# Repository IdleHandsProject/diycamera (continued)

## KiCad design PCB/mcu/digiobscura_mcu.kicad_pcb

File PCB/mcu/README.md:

# Sensory_Adaptation_Bot
A Neural network robot for learning new sensors without programming them specifically.

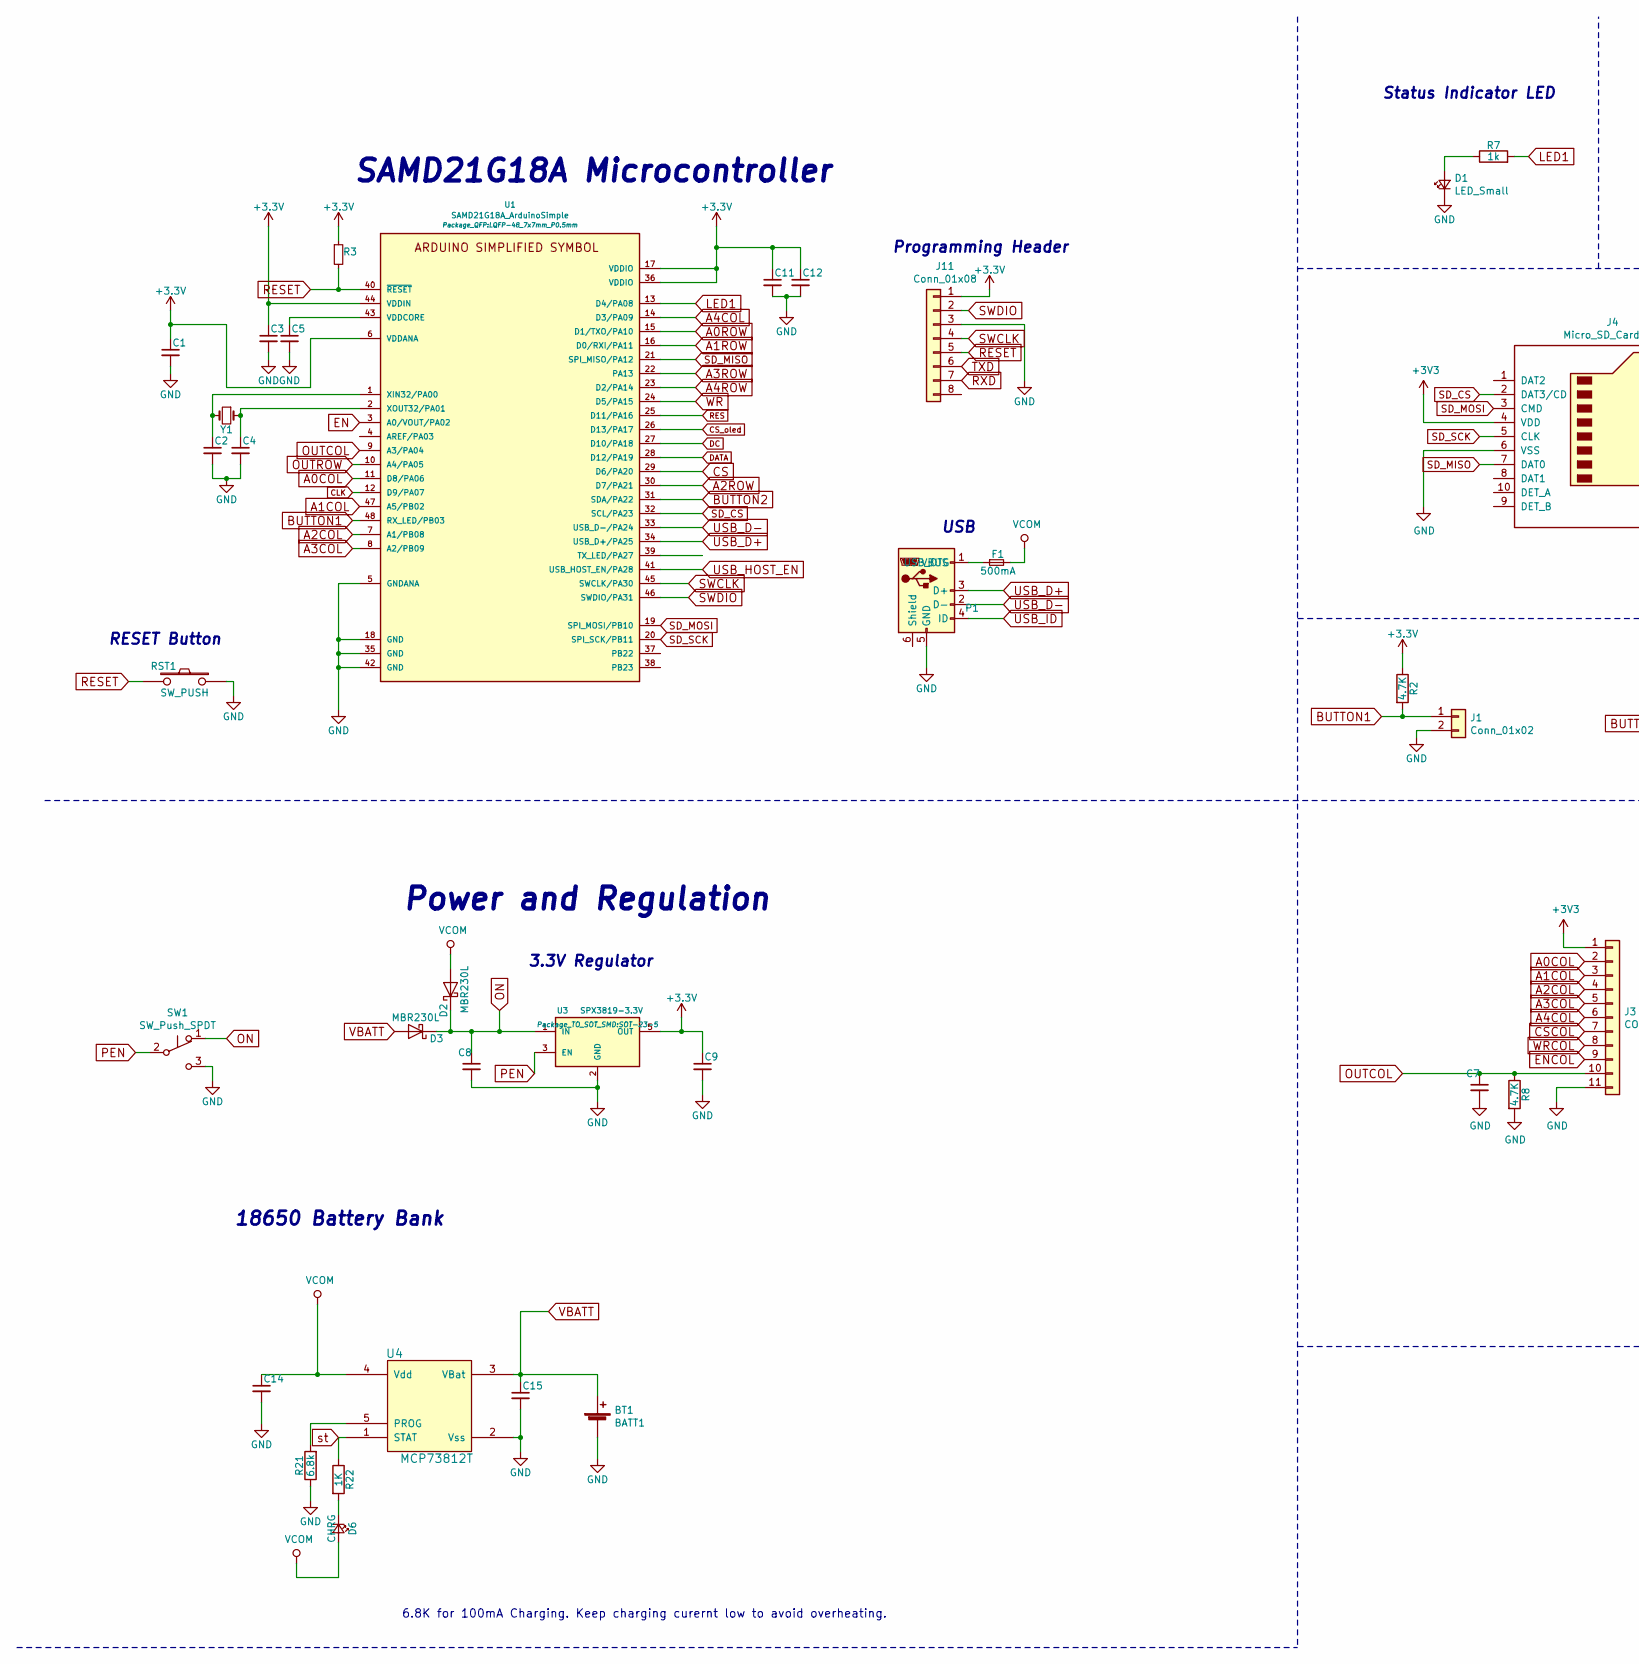
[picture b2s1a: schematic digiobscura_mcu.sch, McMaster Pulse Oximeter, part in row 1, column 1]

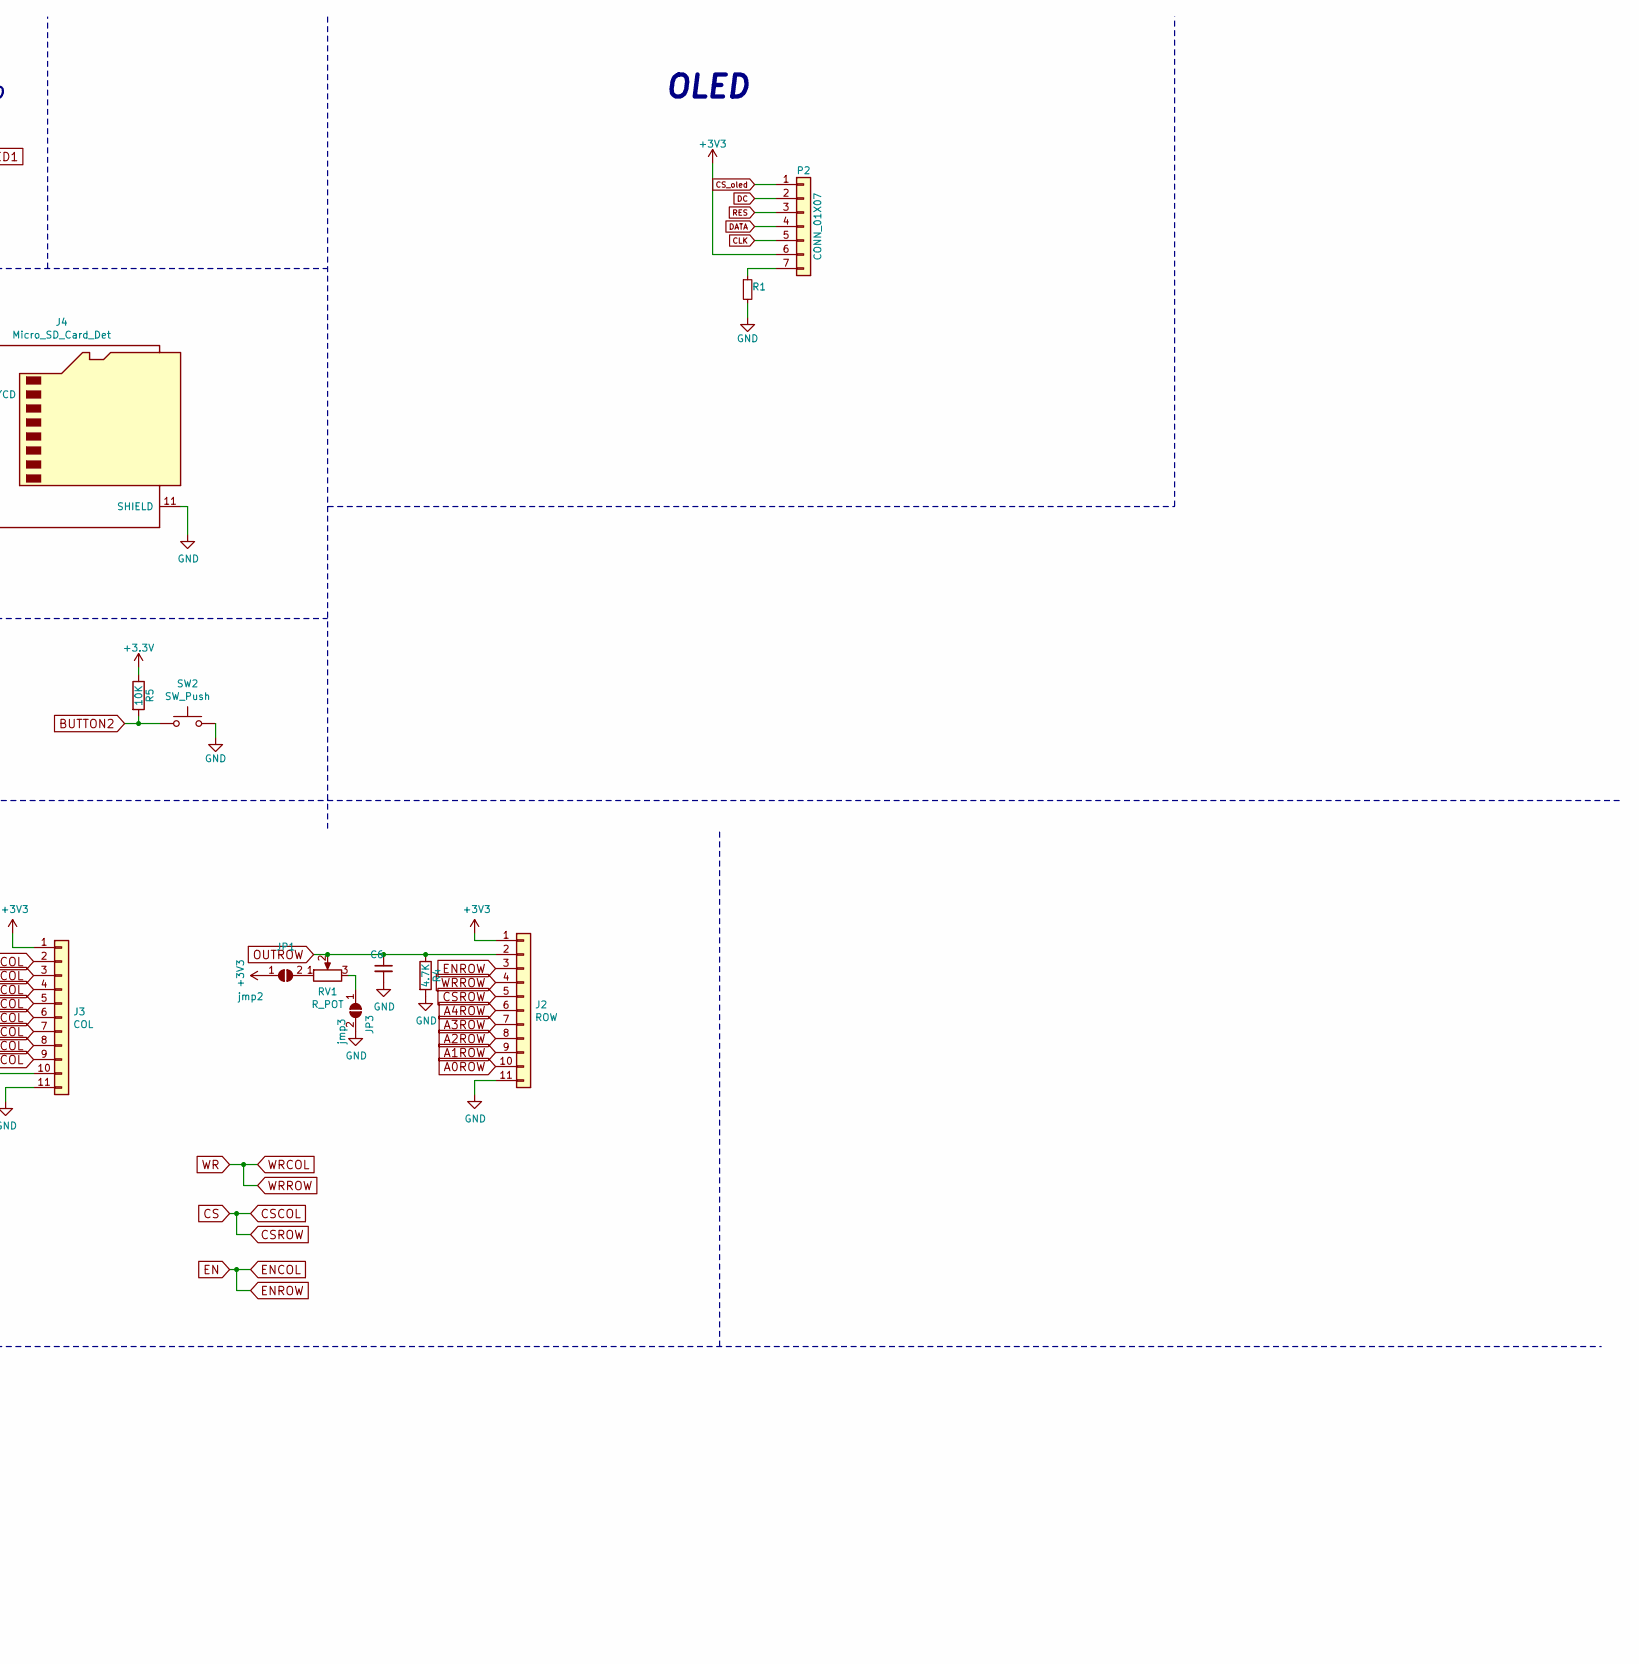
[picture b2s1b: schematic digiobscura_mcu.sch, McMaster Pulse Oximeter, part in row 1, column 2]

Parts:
BT1: BATT1; BatteryHolder_Keystone_1042_1x18650; Digikey Part No. 36-1042P-ND
C1, C3, C5, C11, C12: 0.1uF; C_0805_2012Metric; Digikey Part No. 1276-1286-1-ND
C2, C4: 22pF; C_0805_2012Metric; Digikey Part No. 311-1103-1-ND
C6, C7, C8: 1uF; C_0805_2012Metric; Digikey Part No. 1276-3010-1-ND
C9: 2.2uF; C_0805_2012Metric; Digikey Part No. 311-1463-1-ND
C14, C15: 4.7uF; C_0805_2012Metric; Digikey Part No. 311-1371-1-ND
D1: LED_Small; LED_0603_1608Metric
D2, D3: MBR230L; D_SOD-123F; Digikey Part No. MBR230LSFT1GOSCT-ND
D6: CHRG; LED_0805_2012Metric; Digikey Part No. 160-1436-1-ND
F1: 500mA; Fuse_1210_3225Metric; Digikey Part No. 507-1803-1-ND
J1: Conn_01x02; JST_PH_S2B-PH-K_1x02_P2.00mm_Horizontal
J2: ROW; PinSocket_1x11_P2.54mm_Vertical
J3: COL; PinSocket_1x11_P2.54mm_Vertical
J4: Micro_SD_Card_Det; microSD_HC_Hirose_DM3D-SF; Digikey Part No. HR1941CT-ND
J11: Conn_01x08; PinSocket_1x08_P2.54mm_Vertical
JP1: jmp2; SolderJumper-2_P1.3mm_Open_RoundedPad1.0x1.5mm
JP3: jmp3; SolderJumper-2_P1.3mm_Open_RoundedPad1.0x1.5mm
P1: USB_OTG; USB_Micro-B_Molex-105017-0001; Digikey Part No. 455-1752-1-ND
P2: CONN_01X07; PinSocket_1x07_P2.54mm_Vertical
R1: 100k; R_0805_2012Metric; Digikey Part No. 311-100KLRCT-ND
R2, R4, R8: 4.7K; R_0805_2012Metric; Digikey Part No. 311-4.7KARCT-ND
R3: 10k; R_0805_2012Metric; Digikey Part No. 311-10KARCT-ND
R5: 10K; R_0805_2012Metric; Digikey Part No. 311-4.7KARCT-ND
R7: 1k; R_0805_2012Metric; Digikey Part No. 311-1.0KARCT-ND
R21: 6.8k; R_0805_2012Metric; Digikey Part No. 311-6.8KARCT-ND
R22: 1K; R_0805_2012Metric; Digikey Part No. 311-1.0KJRCT-ND
RST1: SW_PUSH; SW_SPST_B3U-1000P; Digikey Part No. SW1020CT-ND
RV1: R_POT; Potentiometer_Bourns_PTV09A-1_Single_Vertical
SW1: SW_Push_SPDT; SW_Slide_1P2T_CK_OS102011MS2Q
SW2: SW_Push; SW_SPST_EVPBF
U1: SAMD21G18A_ArduinoSimple; LQFP-48_7x7mm_P0.5mm
U3: SPX3819-3.3V; SOT-23-5; Digikey Part No. 1016-1873-1-ND
U4: MCP73812T; SOT-23-5; Digikey Part No. MCP73812T-420I/OTCT-ND
Y1: Crystal_Small; Crystal_SMD_3215-2Pin_3.2x1.5mm; Digikey Part No. XC1617CT-ND

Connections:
A0COL: J3.2, U1.11 (D8/PA06)
A0ROW: J2.10, U1.15 (D1/TXO/PA10)
A1COL: J3.3, U1.47 (A5/PB02)
A1ROW: J2.9, U1.16 (D0/RXI/PA11)
A2COL: J3.4, U1.7 (A1/PB08)
A2ROW: J2.8, U1.30 (D7/PA21)
A3COL: J3.5, U1.8 (A2/PB09)
A3ROW: J2.7, U1.22 (PA13)
A4COL: J3.6, U1.14 (D3/PA09)
A4ROW: J2.6, U1.23 (D2/PA14)
BUTTON1: J1.1, R2.2, U1.48 (RX_LED/PB03)
BUTTON2: R5.2, SW2.1, U1.31 (SDA/PA22)
CLK: P2.5, U1.12 (D9/PA07)
CS: J2.5, J3.7, U1.29 (D6/PA20)
CS_oled: P2.1, U1.26 (D13/PA17)
DATA: P2.4, U1.28 (D12/PA19)
DC: P2.2, U1.27 (D10/PA18)
EN: J2.3, J3.9, U1.3 (A0/VOUT/PA02)
GND: BT1.2 (-), C1.2, C2.2, C3.2, C4.2, C5.2, C6.2, C7.2, C8.2, C9.2, C11.2, C12.2, C14.2, C15.2, D1.1 (K), J1.2, J2.11, J3.11, J4.6 (VSS), J4.11 (SHIELD), J11.3, JP3.2 (B), P1.5 (GND), R1.2, R4.2, R8.2, R21.1, RST1.1, SW1.3 (C), SW2.2, U1.5 (GNDANA), U1.18 (GND), U1.35 (GND), U1.42 (GND), U3.2 (GND), U4.2 (Vss)
LED1: R7.2, U1.13 (D4/PA08)
unnamed: C2.1, U1.1 (XIN32/PA00), Y1.2
unnamed: C4.1, U1.2 (XOUT32/PA01), Y1.1
unnamed: C5.1, U1.43 (VDDCORE)
unnamed: D1.2 (A), R7.1
unnamed: D6.1 (K), R22.2
unnamed: F1.1, P1.1 (VBUS)
unnamed: JP1.2 (B), RV1.1
unnamed: JP3.1 (A), RV1.3
unnamed: P2.7, R1.1
unnamed: R21.2, U4.5 (PROG)
ON: C8.1, D2.1 (K), D3.1 (K), SW1.1 (A), U3.1 (IN)
OUTCOL: C7.1, J3.10, R8.1, U1.9 (A3/PA04)
OUTROW: C6.1, J2.2, R4.1, RV1.2, U1.10 (A4/PA05)
PEN: SW1.2 (B), U3.3 (EN)
RES: P2.3, U1.25 (D11/PA16)
RESET: J11.5, R3.2, RST1.2, U1.40 (~RESET~)
RXD: J11.7
SD_CS: J4.2 (DAT3/CD), U1.32 (SCL/PA23)
SD_MISO: J4.7 (DAT0), U1.21 (SPI_MISO/PA12)
SD_MOSI: J4.3 (CMD), U1.19 (SPI_MOSI/PB10)
SD_SCK: J4.5 (CLK), U1.20 (SPI_SCK/PB11)
SWCLK: J11.4, U1.45 (SWCLK/PA30)
SWDIO: J11.2, U1.46 (SWDIO/PA31)
TXD: J11.6
USB_D+: P1.3 (D+), U1.34 (USB_D+/PA25)
USB_D-: P1.2 (D-), U1.33 (USB_D-/PA24)
USB_HOST_EN: U1.41 (USB_HOST_EN/PA28)
USB_ID: P1.4 (ID)
VBATT: BT1.1 (+), C15.1, D3.2 (A), U4.3 (VBat)
VCOM: C14.1, D2.2 (A), D6.2 (A), F1.2, U4.4 (Vdd)
WR: J2.4, J3.8, U1.24 (D5/PA15)
st: R22.1, U4.1 (STAT)

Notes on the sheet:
USB
18650 Battery Bank
SAMD21G18A Microcontroller
Power and Regulation
Programming Header
3.3V Regulator
Status Indicator LED
RESET Button
6.8K for 100mA Charging. Keep charging curernt low to avoid overheating.
OLED

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
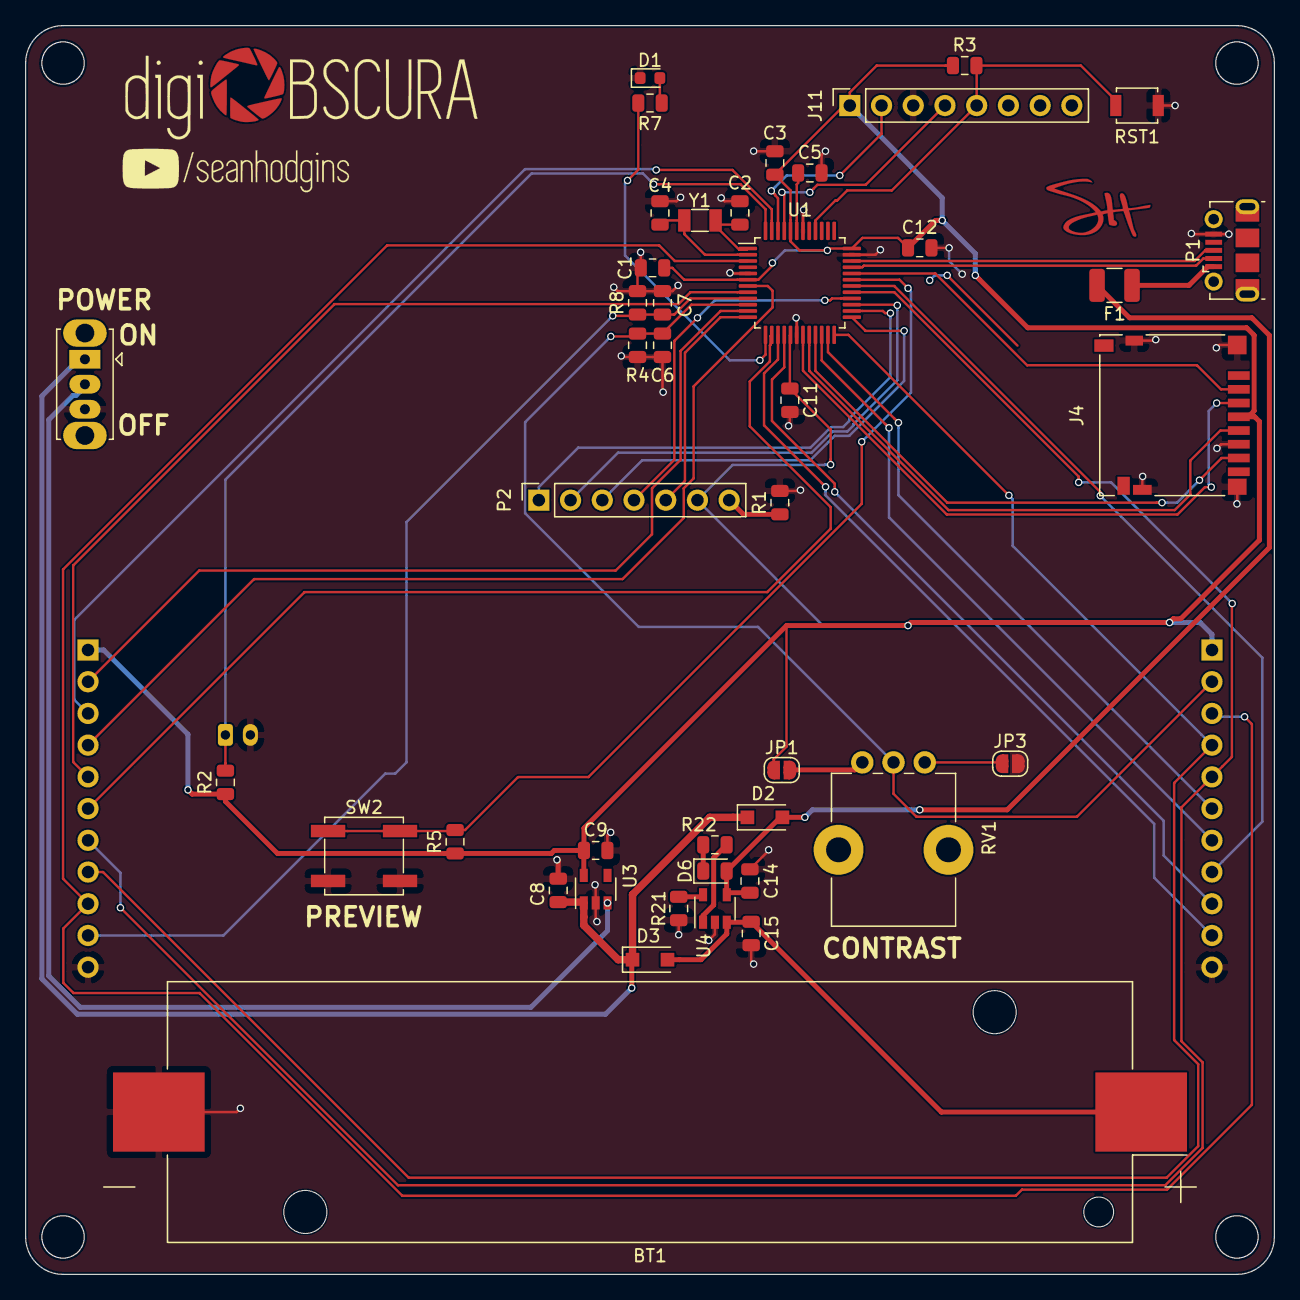
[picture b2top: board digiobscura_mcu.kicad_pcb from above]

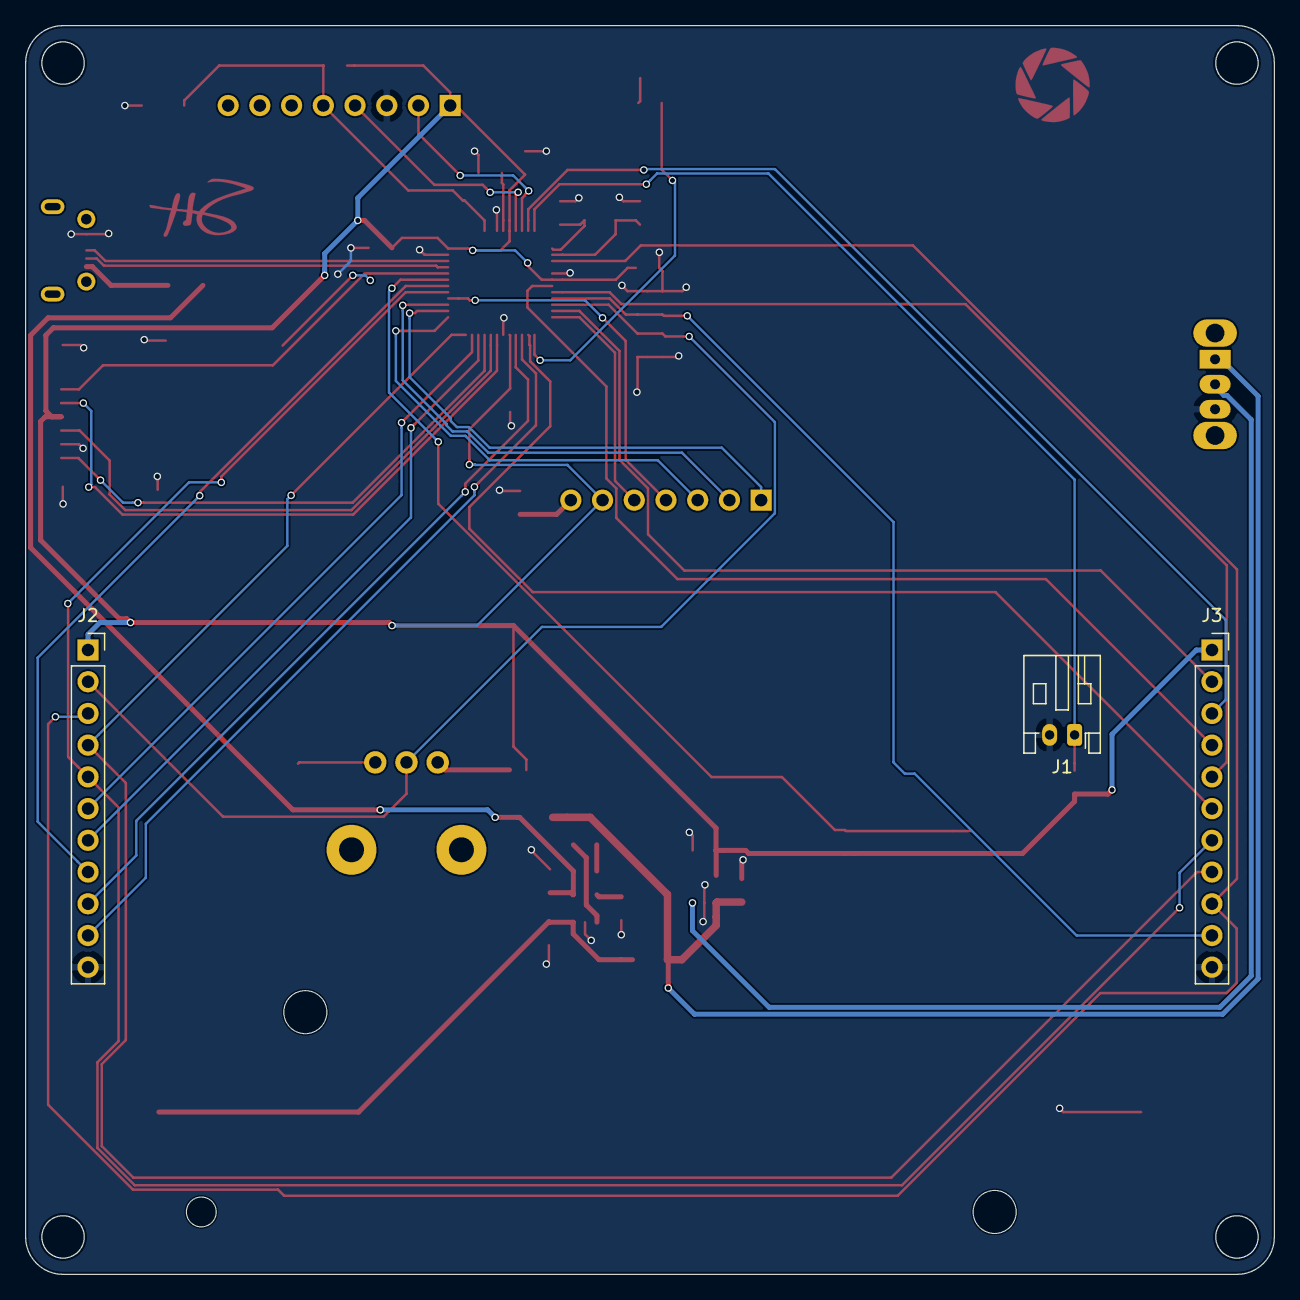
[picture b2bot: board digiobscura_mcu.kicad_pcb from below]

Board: 2 copper layers, 100.0 x 100.0 mm, 45 parts (3 on the bottom side), 49 nets.

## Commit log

2019-12-27 readme update
2019-12-28 F3D Files added
2019-12-28 Fixed BOM
2020-01-02 updated BOM files
2020-01-02 Added link to BOM
